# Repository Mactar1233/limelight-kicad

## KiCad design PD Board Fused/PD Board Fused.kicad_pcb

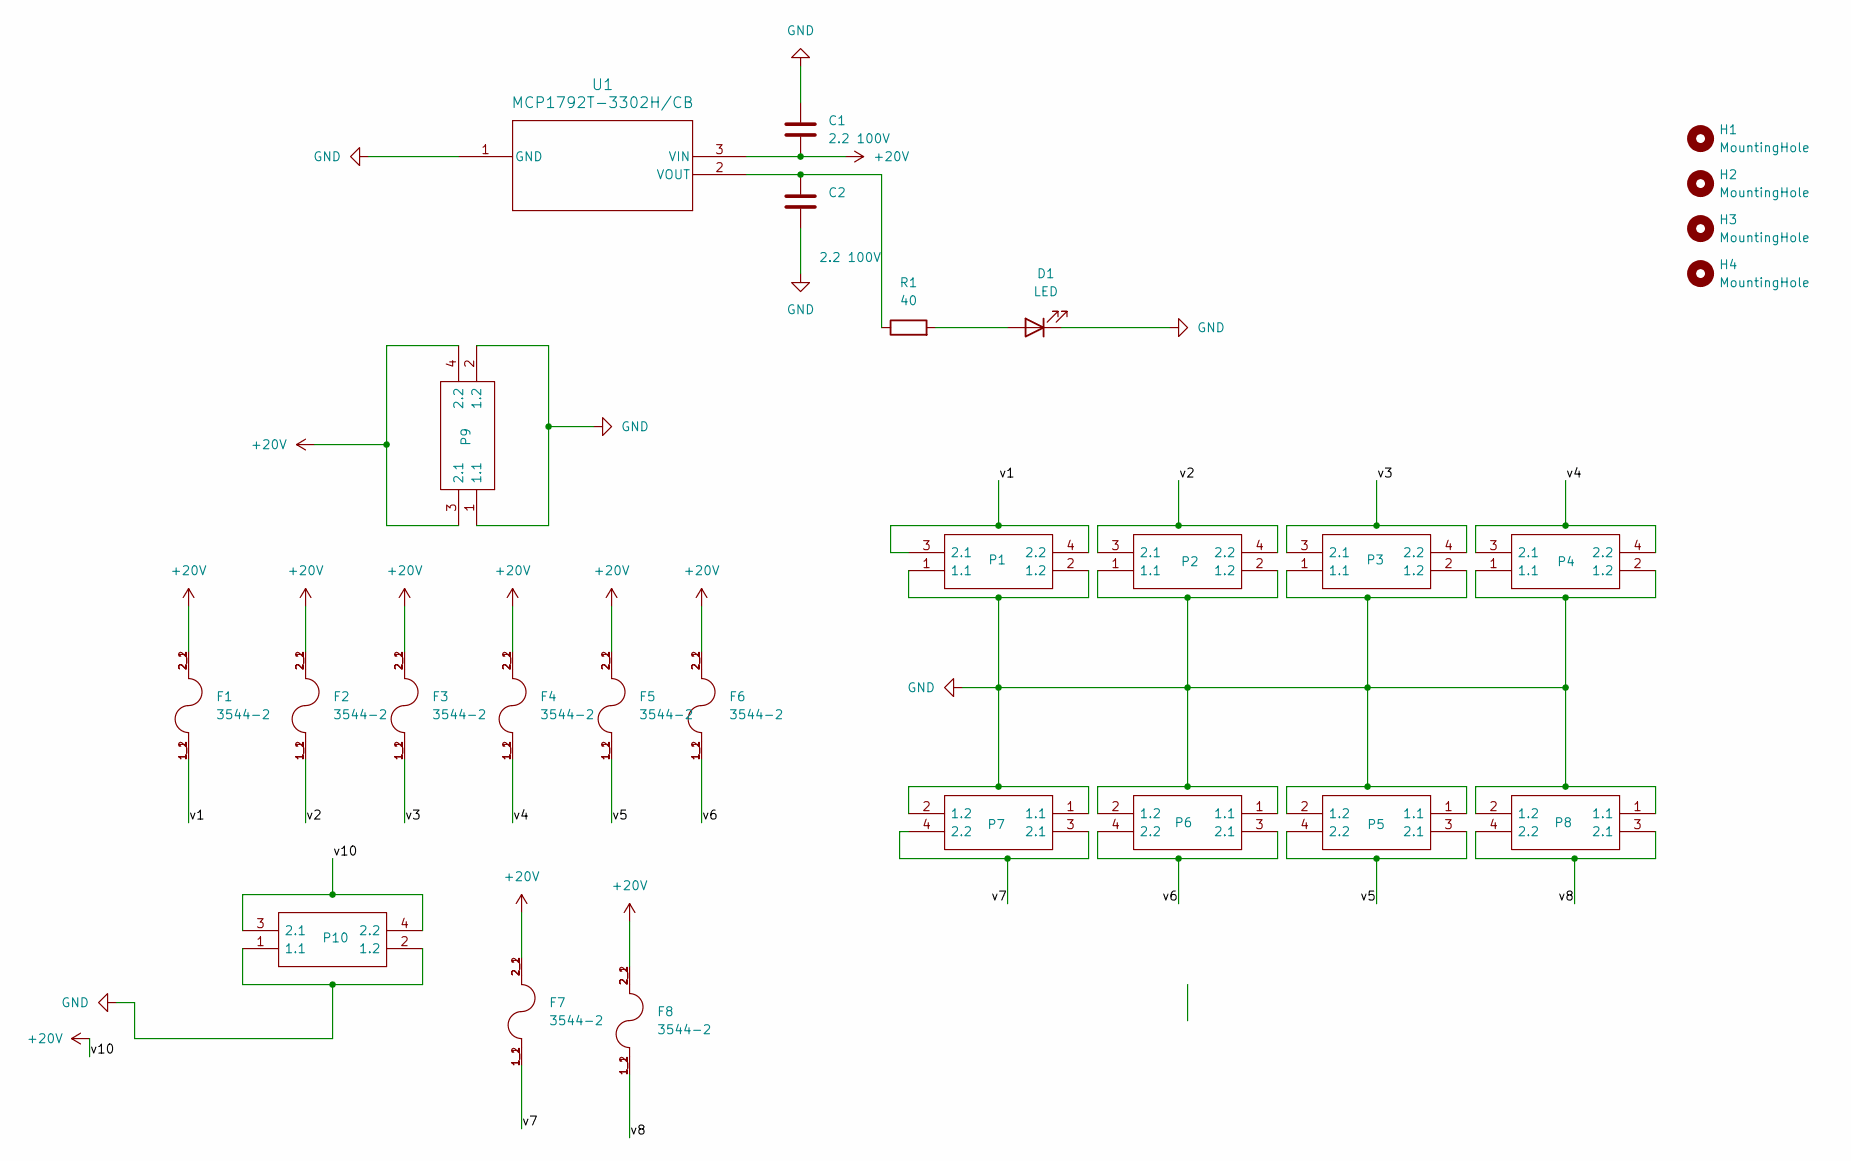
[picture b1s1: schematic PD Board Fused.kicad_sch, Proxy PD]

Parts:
C1, C2: 2.2 100V; C_0805_2012Metric; LCSC Part # C2981733
D1: LED; LTST-C930; LCSC Part # C125111
F1, F2, F3, F4, F5, F6, F7, F8: 3544-2; FUSE_3544-2; PARTREV C
H1, H2, H3, H4: MountingHole; MountingHole_2.5mm
P1, P2, P3, P4, P5, P6, P7, P8, P9, P10: 2604-1102; 26041102; Manufacturer_Part_Number 2604-1102; LCSC Part # C3309286
R1: 40; R_0805_2012Metric; LCSC Part # C114564
U1: MCP1792T-3302H/CB; SOT-23A_CB_MCH; LCSC Part # C625397

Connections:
+20V: C1.2, F1.2_1, F1.2_2, F2.2_1, F2.2_2, F3.2_1, F3.2_2, F4.2_1, F4.2_2, F5.2_1, F5.2_2, F6.2_1, F6.2_2, F7.2_1, F7.2_2, F8.2_1, F8.2_2, P9.3 (2.1), P9.4 (2.2), P10.3 (2.1), P10.4 (2.2), U1.3 (VIN)
/v1: F1.1_1, F1.1_2, P1.3 (2.1), P1.4 (2.2)
/v2: F2.1_1, F2.1_2, P2.3 (2.1), P2.4 (2.2)
/v3: F3.1_1, F3.1_2, P3.3 (2.1), P3.4 (2.2)
/v4: F4.1_1, F4.1_2, P4.3 (2.1), P4.4 (2.2)
/v5: F5.1_1, F5.1_2, P5.3 (2.1), P5.4 (2.2)
/v6: F6.1_1, F6.1_2, P6.3 (2.1), P6.4 (2.2)
/v7: F7.1_1, F7.1_2, P7.3 (2.1), P7.4 (2.2)
/v8: F8.1_1, F8.1_2, P8.3 (2.1), P8.4 (2.2)
GND: C1.1, C2.2, D1.1 (K), P1.1 (1.1), P1.2 (1.2), P2.1 (1.1), P2.2 (1.2), P3.1 (1.1), P3.2 (1.2), P4.1 (1.1), P4.2 (1.2), P5.1 (1.1), P5.2 (1.2), P6.1 (1.1), P6.2 (1.2), P7.1 (1.1), P7.2 (1.2), P8.1 (1.1), P8.2 (1.2), P9.1 (1.1), P9.2 (1.2), P10.1 (1.1), P10.2 (1.2), U1.1 (GND)
unnamed: D1.2 (A), R1.2
unnamed: C2.1, R1.1, U1.2 (VOUT)

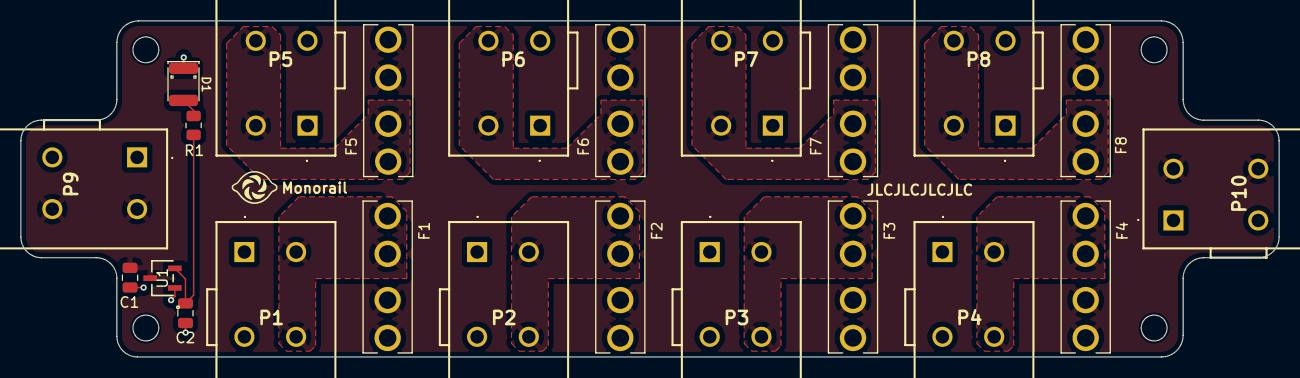
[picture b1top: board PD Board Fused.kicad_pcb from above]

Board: 4 copper layers, 121.7 x 32.5 mm, 27 parts (0 on the bottom side), 12 nets.

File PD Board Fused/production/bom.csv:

Designator,Footprint,Quantity,Value,LCSC Part #
"C1, C2",0805,2,2.2 100V,C2981733
D1,LTST-C930,1,LED,C125111
"F1, F2, F3, F4, F5, F6, F7, F8",FUSE_3544-2,8,3544-2,
"P1, P10, P2, P3, P4, P5, P6, P7, P8, P9",26041102,10,2604-1102,C3309286
R1,0805,1,40,C114564
U1,SOT-23A_CB_MCH,1,MCP1792T-3302H/CB,C625397

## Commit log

2025-08-15 thin pd
2025-08-16 moved tab
2025-08-17 started fused board
2025-08-20 finished monorail
